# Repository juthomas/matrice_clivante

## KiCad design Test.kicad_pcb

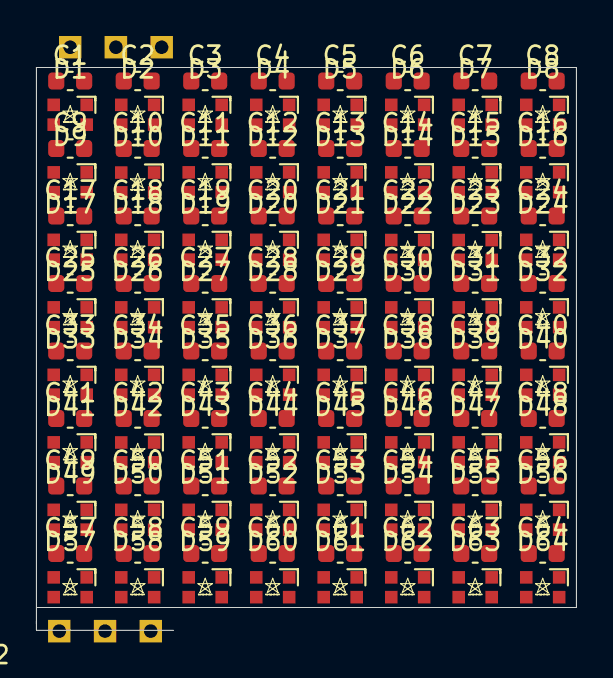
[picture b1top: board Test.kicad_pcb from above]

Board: 2 copper layers, 30.0 x 31.3 mm, 130 parts (0 on the bottom side), 67 nets, no tracks yet.

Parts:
C1, C2, C3, C4, C5, C6, C7, C8, C9, C10, C11, C12, C13, C14, C15, C16, C17, C18, C19, C20, C21, C22, C23, C24, C25, C26, C27, C28, C29, C30, C31, C32, C33, C34, C35, C36, C37, C38, C39, C40, C41, C42, C43, C44, C45, C46, C47, C48, C49, C50, C51, C52, C53, C54, C55, C56, C57, C58, C59, C60, C61, C62, C63, C64: 100nf; C_0603_1608Metric
D1, D2, D3, D4, D5, D6, D7, D8, D9, D10, D11, D12, D13, D14, D15, D16, D17, D18, D19, D20, D21, D22, D23, D24, D25, D26, D27, D28, D29, D30, D31, D32, D33, D34, D35, D36, D37, D38, D39, D40, D41, D42, D43, D44, D45, D46, D47, D48, D49, D50, D51, D52, D53, D54, D55, D56, D57, D58, D59, D60, D61, D62, D63, D64: WS2812-2020
U1: Input_Matrice_8x8_WS2812-2020; Input-connector
U2: Output_Matrice_8x8_WS2812-2020; Input-connector

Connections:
+5V: C1.1, C2.1, C3.1, C4.1, C5.1, C6.1, C7.1, C8.1, C9.1, C10.1, C11.1, C12.1, C13.1, C14.1, C15.1, C16.1, C17.1, C18.1, C19.1, C20.1, C21.1, C22.1, C23.1, C24.1, C25.1, C26.1, C27.1, C28.1, C29.1, C30.1, C31.1, C32.1, C33.1, C34.1, C35.1, C36.1, C37.1, C38.1, C39.1, C40.1, C41.1, C42.1, C43.1, C44.1, C45.1, C46.1, C47.1, C48.1, C49.1, C50.1, C51.1, C52.1, C53.1, C54.1, C55.1, C56.1, C57.1, C58.1, C59.1, C60.1, C61.1, C62.1, C63.1, C64.1, D1.4, D2.4, D3.4, D4.4, D5.4, D6.4, D7.4, D8.4, D9.4, D10.4, D11.4, D12.4, D13.4, D14.4, D15.4, D16.4, D17.4, D18.4, D19.4, D20.4, D21.4, D22.4, D23.4, D24.4, D25.4, D26.4, D27.4, D28.4, D29.4, D30.4, D31.4, D32.4, D33.4, D34.4, D35.4, D36.4, D37.4, D38.4, D39.4, D40.4, D41.4, D42.4, D43.4, D44.4, D45.4, D46.4, D47.4, D48.4, D49.4, D50.4, D51.4, D52.4, D53.4, D54.4, D55.4, D56.4, D57.4, D58.4, D59.4, D60.4, D61.4, D62.4, D63.4, D64.4, U1.2, U2.2
/Led Set1/DIN: D1.3, U1.1
/sheet5FFCCB65/DIN: D1.1, D2.3
/sheet5FFCCCDC/DIN: D2.1, D3.3
/sheet5FFCCEA1/DIN: D3.1, D4.3
/sheet5FFCD054/DIN: D4.1, D5.3
/sheet5FFCD56C/DIN: D6.1, D7.3
/sheet5FFCD275/DIN: D5.1, D6.3
/sheet5FFCD801/DIN: D7.1, D8.3
/sheet5FFCE96D/DIN: D8.1, D9.3
/sheet5FFCE96E/DIN: D9.1, D10.3
/sheet5FFCE96F/DIN: D10.1, D11.3
/sheet5FFCE970/DIN: D11.1, D12.3
/sheet5FFCE971/DIN: D12.1, D13.3
/sheet5FFCE972/DIN: D13.1, D14.3
/sheet5FFCE973/DIN: D14.1, D15.3
/sheet5FFCE974/DIN: D15.1, D16.3
/sheet5FFCF15A/DIN: D17.1, D18.3
/sheet5FFCF15B/DIN: D18.1, D19.3
/sheet5FFCF15C/DIN: D19.1, D20.3
/sheet5FFCF15D/DIN: D20.1, D21.3
/sheet5FFCF15E/DIN: D21.1, D22.3
/sheet5FFCF15F/DIN: D22.1, D23.3
/sheet5FFCF159/DIN: D16.1, D17.3
/sheet5FFCF160/DIN: D23.1, D24.3
/sheet5FFCFCC1/DIN: D24.1, D25.3
/sheet5FFCFCC2/DIN: D25.1, D26.3
/sheet5FFCFCC3/DIN: D26.1, D27.3
/sheet5FFCFCC4/DIN: D27.1, D28.3
/sheet5FFCFCC5/DIN: D28.1, D29.3
/sheet5FFCFCC6/DIN: D29.1, D30.3
/sheet5FFCFCC7/DIN: D30.1, D31.3
/sheet5FFCFCC8/DIN: D31.1, D32.3
/sheet5FFD0AB9/DIN: D32.1, D33.3
/sheet5FFD0ABA/DIN: D33.1, D34.3
/sheet5FFD0ABB/DIN: D34.1, D35.3
/sheet5FFD0ABC/DIN: D35.1, D36.3
/sheet5FFD0ABD/DIN: D36.1, D37.3
/sheet5FFD0ABE/DIN: D37.1, D38.3
/sheet5FFD0ABF/DIN: D38.1, D39.3
/sheet5FFD0AC0/DIN: D39.1, D40.3
/sheet5FFD1E5A/DIN: D45.1, D46.3
/sheet5FFD1E5B/DIN: D46.1, D47.3
/sheet5FFD1E5C/DIN: D47.1, D48.3
/sheet5FFD1E55/DIN: D40.1, D41.3
/sheet5FFD1E56/DIN: D41.1, D42.3
/sheet5FFD1E57/DIN: D42.1, D43.3
/sheet5FFD1E58/DIN: D43.1, D44.3
/sheet5FFD1E59/DIN: D44.1, D45.3
/sheet5FFD364A/DIN: D49.1, D50.3
/sheet5FFD364B/DIN: D50.1, D51.3
/sheet5FFD364C/DIN: D51.1, D52.3
/sheet5FFD364D/DIN: D52.1, D53.3
/sheet5FFD364E/DIN: D53.1, D54.3
/sheet5FFD364F/DIN: D54.1, D55.3
/sheet5FFD558A/DIN: D57.1, D58.3
/sheet5FFD558B/DIN: D58.1, D59.3
/sheet5FFD558C/DIN: D59.1, D60.3
/sheet5FFD558D/DIN: D60.1, D61.3
/sheet5FFD558E/DIN: D61.1, D62.3
/sheet5FFD558F/DIN: D62.1, D63.3
/sheet5FFD3649/DIN: D48.1, D49.3
/sheet5FFD3650/DIN: D55.1, D56.3
/sheet5FFD5589/DIN: D56.1, D57.3
/sheet5FFD5590/DIN: D63.1, D64.3
/sheet5FFD5590/DOUT: D64.1, U2.1
GND: C1.2, C2.2, C3.2, C4.2, C5.2, C6.2, C7.2, C8.2, C9.2, C10.2, C11.2, C12.2, C13.2, C14.2, C15.2, C16.2, C17.2, C18.2, C19.2, C20.2, C21.2, C22.2, C23.2, C24.2, C25.2, C26.2, C27.2, C28.2, C29.2, C30.2, C31.2, C32.2, C33.2, C34.2, C35.2, C36.2, C37.2, C38.2, C39.2, C40.2, C41.2, C42.2, C43.2, C44.2, C45.2, C46.2, C47.2, C48.2, C49.2, C50.2, C51.2, C52.2, C53.2, C54.2, C55.2, C56.2, C57.2, C58.2, C59.2, C60.2, C61.2, C62.2, C63.2, C64.2, D1.2, D2.2, D3.2, D4.2, D5.2, D6.2, D7.2, D8.2, D9.2, D10.2, D11.2, D12.2, D13.2, D14.2, D15.2, D16.2, D17.2, D18.2, D19.2, D20.2, D21.2, D22.2, D23.2, D24.2, D25.2, D26.2, D27.2, D28.2, D29.2, D30.2, D31.2, D32.2, D33.2, D34.2, D35.2, D36.2, D37.2, D38.2, D39.2, D40.2, D41.2, D42.2, D43.2, D44.2, D45.2, D46.2, D47.2, D48.2, D49.2, D50.2, D51.2, D52.2, D53.2, D54.2, D55.2, D56.2, D57.2, D58.2, D59.2, D60.2, D61.2, D62.2, D63.2, D64.2, U1.3, U2.3

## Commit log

2021-01-05 [ADD] matrice clivante
